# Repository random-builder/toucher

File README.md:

# Toucher

### Purpose

Provides bed leveling FSR sensor controller for square heat beds.

### Features

- 4 sensor points
- 85C maximum bed temperature
- serial/usb terminal command interface
- flexible controller configuration and logging
- connects in place of mechanical endstop switch on Z

### Materials

Uses [Arduino Nano](https://github.com/random-builder/toucher/blob/master/docs/nano-pinout.pdf)
with [FSR-402](https://github.com/random-builder/toucher/blob/master/docs/FSR-402.pdf) sensors.
See [schema.pdf](https://github.com/random-builder/fsr-endstop/blob/master/schema/schema.pdf).

### Algorithm

Tracks fast and slow exponential averages for all channels 
to detect summary averages cross-over events.

### Reference Glass Mount

Provides "floating suspension",
when horizontal mount forces are maximal, 
vertical mount forces are minimal,
and there is a small downward force inclination.

Model: [Level: Wanhao D6 Glass Sheet Mount](https://www.thingiverse.com/thing:2461546)

### Reference Marlin Build

Works on Wanhao D6 / Monoprice Clone printer.

Github branch: [Random Builder / wanhao-d6-probe](https://github.com/random-builder/Marlin/tree/wanhao-d6-probe)

### Similar Projects

Github project: [John Socha-Leialoha FSR Endstop](https://github.com/JohnSL/FSR_Endstop)

### Setup Instructions

See [wiki page](https://github.com/random-builder/fsr-endstop/wiki).

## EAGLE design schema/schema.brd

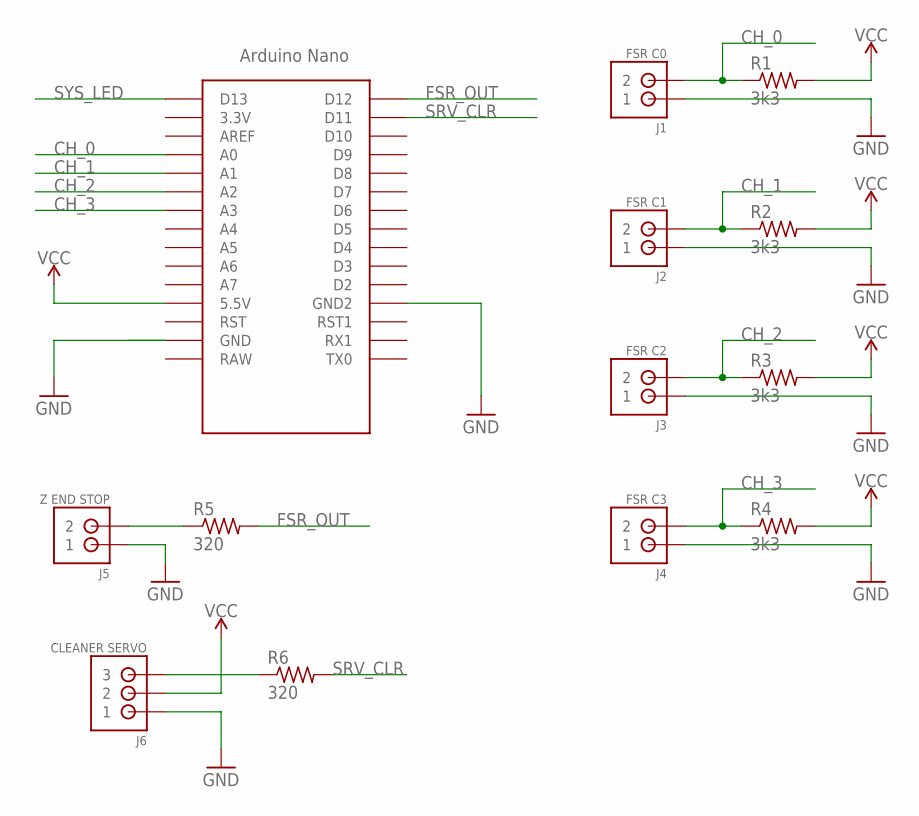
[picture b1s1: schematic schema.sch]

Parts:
J1: FSR C0; JST_B2B-PH_HEADER
J2: FSR C1; JST_B2B-PH_HEADER
J3: FSR C2; JST_B2B-PH_HEADER
J4: FSR C3; JST_B2B-PH_HEADER
J5: Z END STOP; JST_B2B-PH_HEADER
J6: CLEANER SERVO; JST_B3B-PH_HEADER
R1, R2, R3, R4: 3k3; 0204/5
R5, R6: 320; 0204/5
U$1: NANO

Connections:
CH_0: J1.P2 (2), R1.1, U$1.A0
CH_1: J2.P2 (2), R2.1, U$1.A1
CH_2: J3.P2 (2), R3.1, U$1.A2
CH_3: J4.P2 (2), R4.1, U$1.A3
FSR_OUT: R5.2, U$1.D12
GND: J1.P1 (1), J2.P1 (1), J3.P1 (1), J4.P1 (1), J5.P1 (1), J6.P1 (1), U$1.GND, U$1.GND1 (GND2)
unnamed: J6.P3 (3), R6.1
unnamed: J5.P2 (2), R5.1
SRV_CLR: R6.2, U$1.D11
SYS_LED: U$1.D13
VCC: J6.P2 (2), R1.2, R2.2, R3.2, R4.2, U$1.5V (5.5V)

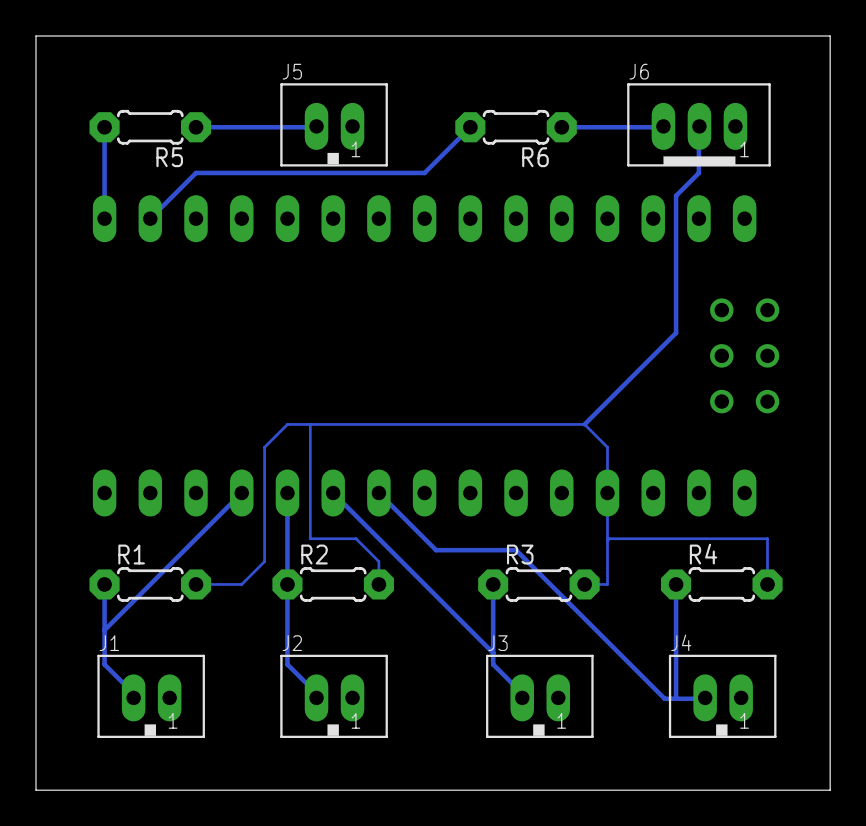
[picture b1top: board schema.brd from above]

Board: 2 copper layers, 44.1 x 41.9 mm, 13 parts (0 on the bottom side), 10 nets.

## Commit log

2017-08-01 develop
2017-08-02 logging

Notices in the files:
parts and their libraries:
SparkFun-PowerSymbols: Licensing: Creative Commons ShareAlike 4.0 International - https://creativecommons.org/licenses/by-sa/4.0
